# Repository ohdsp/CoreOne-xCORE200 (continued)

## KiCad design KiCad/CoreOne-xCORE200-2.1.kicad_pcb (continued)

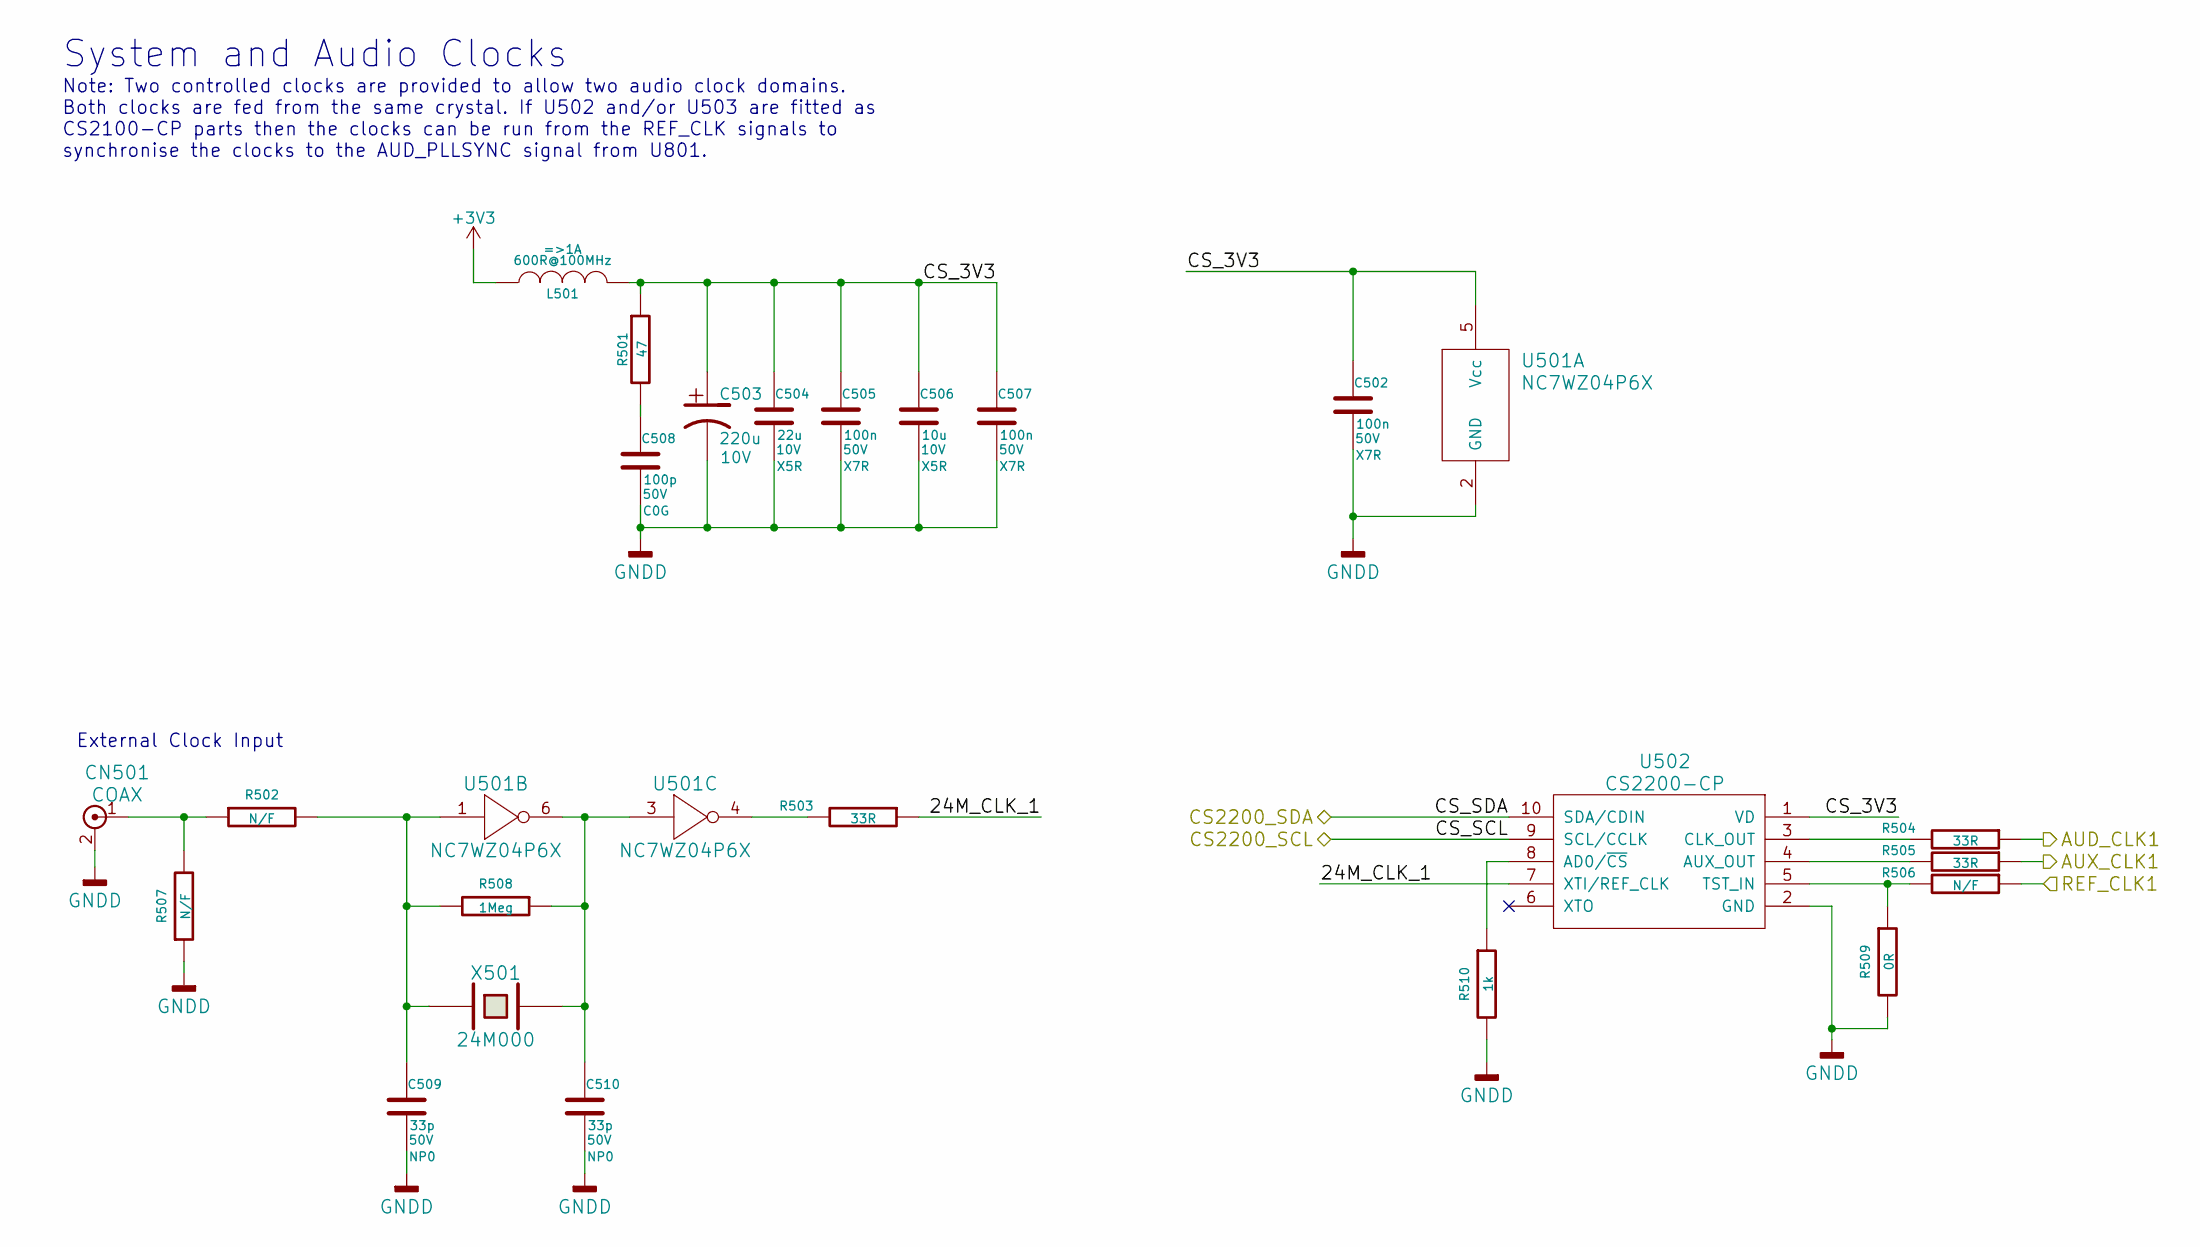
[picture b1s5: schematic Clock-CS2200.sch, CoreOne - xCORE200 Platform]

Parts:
C502, C505, C507: 100n; SMD-0805; Voltage 50V; Tolerance 10%
C503: 220u; CAP-TH-D6.3mmP2.5mm; Voltage 10V
C504: 22u; SMD-0805; Voltage 10V; Tolerance 20%
C506: 10u; SMD-0805; Voltage 10V; Tolerance 20%
C508: 100p; SMD-0805; Voltage 50V; Tolerance 5%
C509, C510: 33p; SMD-0805; Voltage 50V; Tolerance 5%
CN501: COAX; CONN_SIL_2_1MM
L501: 600R@100MHz; SMD-0805
R501: 47; SMD-0805; Tolerance 1%
R502, R506, R507: N/F; SMD-0805; Tolerance 1%
R503, R504, R505: 33R; SMD-0805; Tolerance 1%
R508: 1Meg; SMD-0805; Tolerance 1%
R509: 0R; SMD-0805; Tolerance 1%
R510: 1k; SMD-0805; Tolerance 1%
U501: NC7WZ04P6X; IC-SC70-6
U502: CS2200-CP; IC-MSOP-10
X501: 24M000; XTAL_HC49_TH

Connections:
/AUD_CLK1: R504.1; also elsewhere on the board
/AUD_PLLSYNC: R506.1; also elsewhere on the board
/Clock-CS2200/24M_CLK_1: R503.1, U502.7 (XTI/REF_CLK)
/Clock-CS2200/CS_3V3: C502.1, C503.1, C504.1, C505.1, C506.1, C507.1, L501.2, R501.1, U501.5 (Vcc), U502.1 (VD)
/I2C1_SCL: U502.9 (SCL/CCLK); also elsewhere on the board
/I2C1_SDA: U502.10 (SDA/CDIN); also elsewhere on the board
/SYS_CLK: R505.1; also elsewhere on the board
GNDD: C502.2, C503.2, C504.2, C505.2, C506.2, C507.2, C508.2, C509.2, C510.2, CN501.2, R507.1, R509.2, R510.2, U501.2 (GND), U502.2 (GND); also elsewhere on the board
unnamed: C508.1, R501.2
unnamed: C509.1, R502.2, R508.2, U501.1, X501.1
unnamed: C510.1, R508.1, U501.3, U501.6, X501.2
unnamed: CN501.1, R502.1, R507.2
unnamed: R503.2, U501.4
unnamed: R504.2, U502.3 (CLK_OUT)
unnamed: R505.2, U502.4 (AUX_OUT)
unnamed: R506.2, R509.1, U502.5 (TST_IN)
unnamed: R510.1, U502.8 (AD0/~CS~)

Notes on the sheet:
System and Audio Clocks
External Clock Input
Note: Two controlled clocks are provided to allow two audio clock domains. Both clocks are fed from the same crystal. If U502 and/or U503 are fitted as CS2100-CP parts then the clocks can be run from the REF_CLK signals to synchronise the clocks to the AUD_PLLSYNC signal from U801.

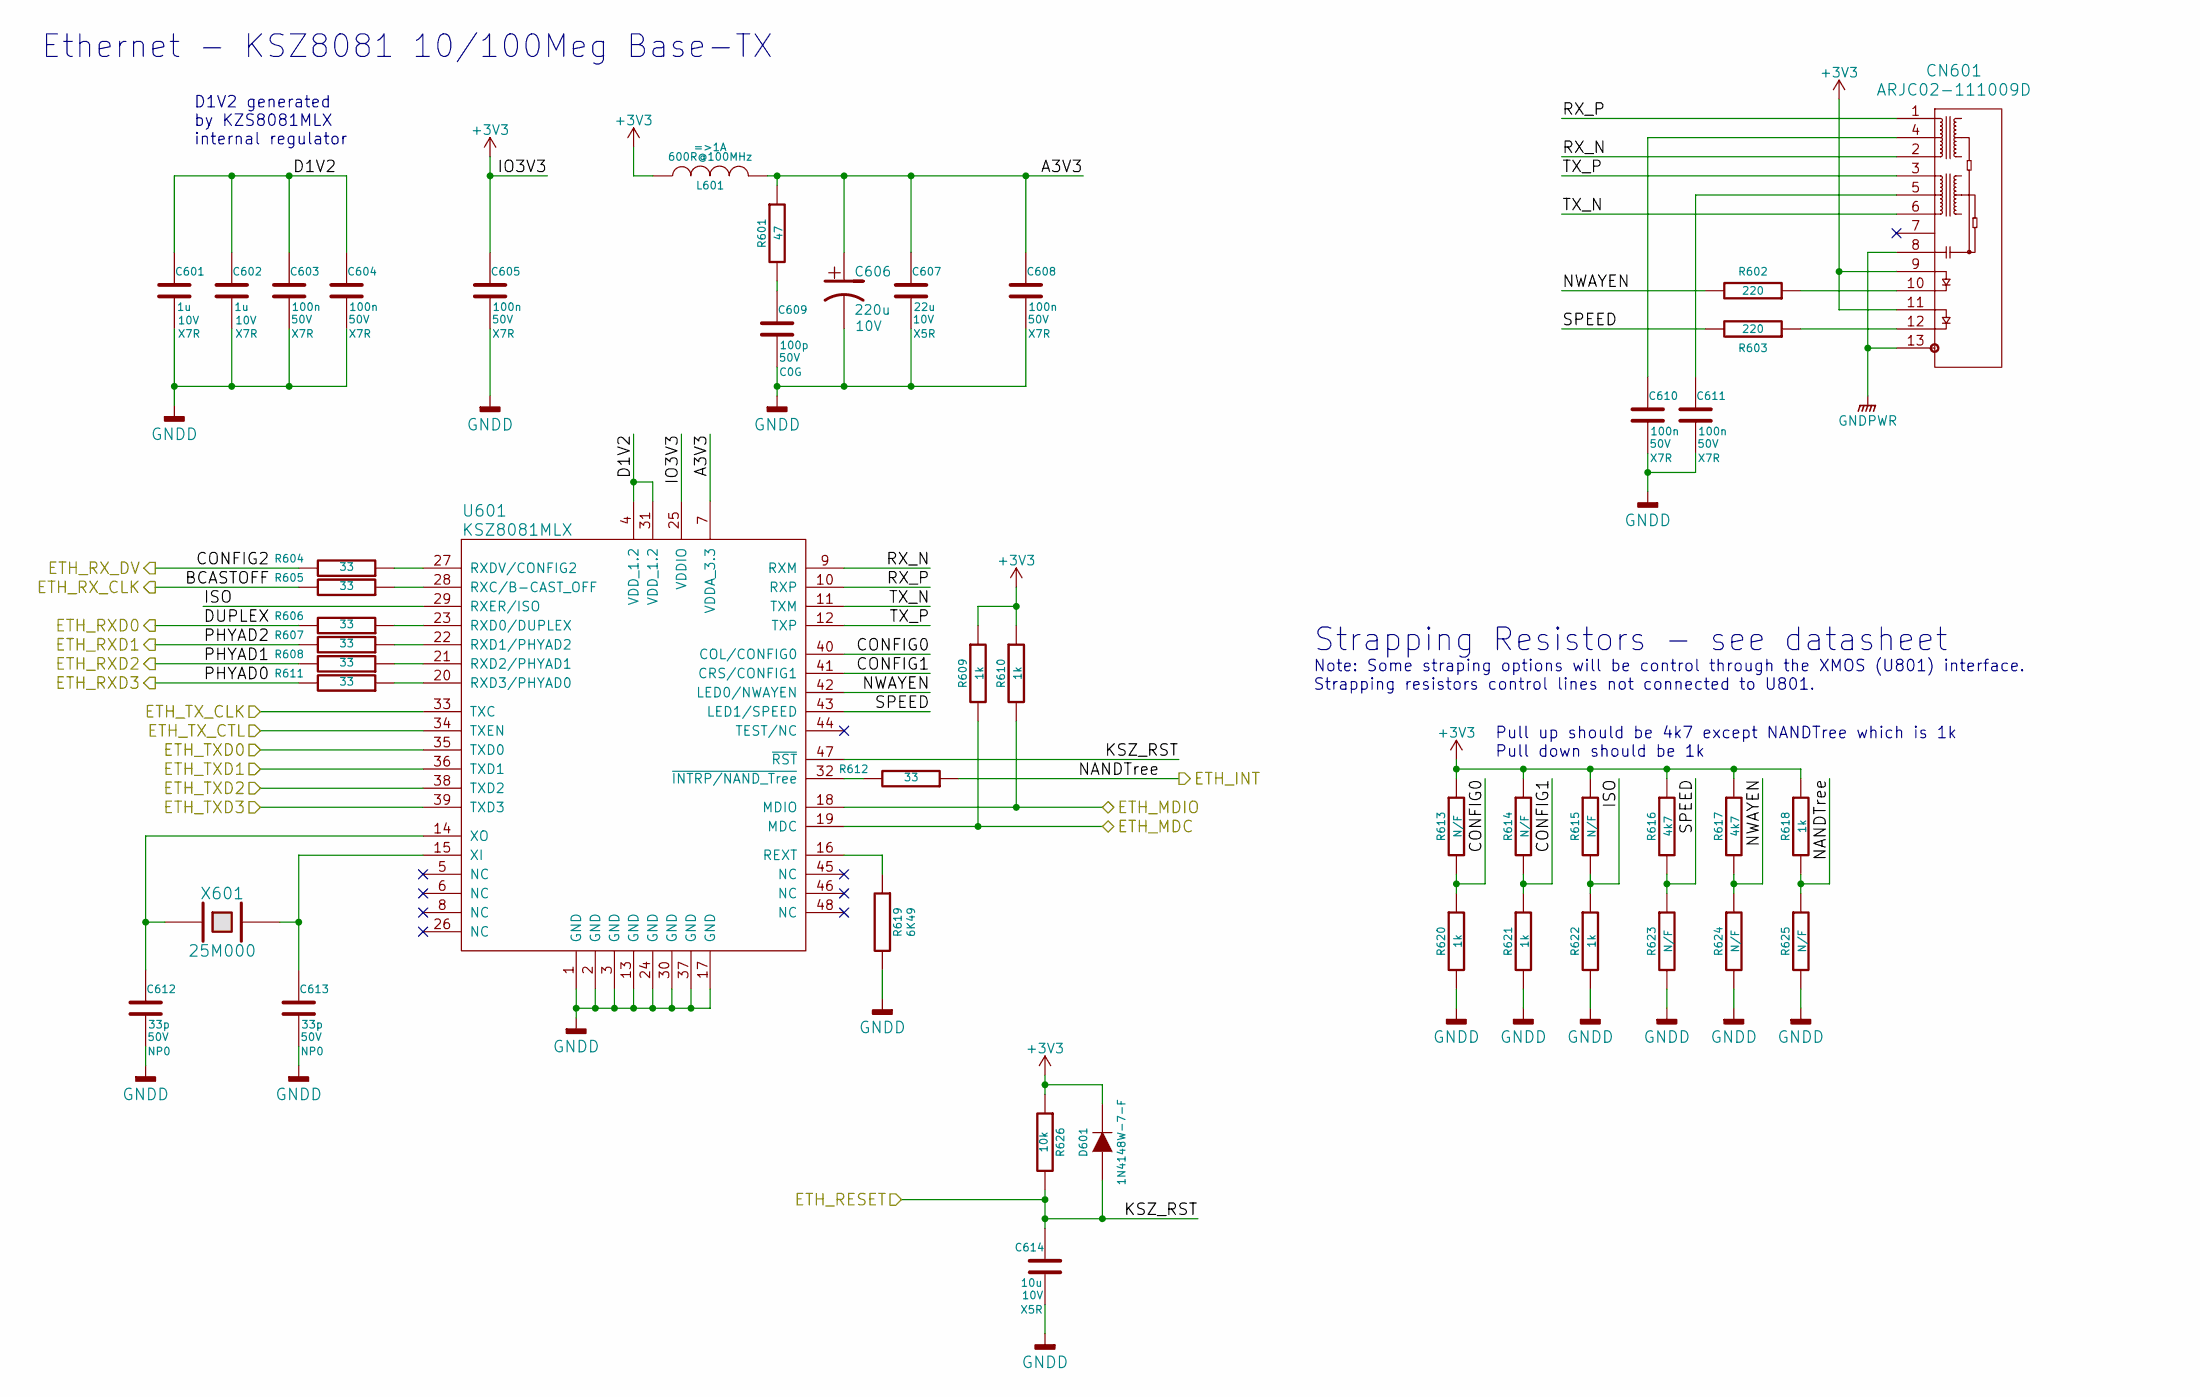
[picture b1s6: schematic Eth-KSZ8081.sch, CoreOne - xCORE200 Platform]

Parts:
C601, C602: 1u; SMD-0805; Voltage 10V; Tolerance 10%
C603, C604, C605, C608, C610, C611: 100n; SMD-0805; Voltage 50V; Tolerance 10%
C606: 220u; CAP-TH-D6.3mmP2.5mm; Voltage 10V
C607: 22u; SMD-0805; Voltage 10V; Tolerance 20%
C609: 100p; SMD-0805; Voltage 50V; Tolerance 5%
C612, C613: 33p; SMD-0805; Voltage 50V; Tolerance 5%
C614: 10u; SMD-0805; Voltage 10V; Tolerance 20%
CN601: ARJC02-111009D; CONN-RJ45-ARJC02-111xxxx
D601: 1N4148W-7-F; DIODE-SOD-123
L601: 600R@100MHz; SMD-0805
R601: 47; SMD-0805; Tolerance 1%
R602, R603: 220; SMD-0805; Tolerance 1%
R604, R605, R606, R607, R608, R611, R612: 33; SMD-0805; Tolerance 1%
R609, R610, R618, R620, R621, R622: 1k; SMD-0805; Tolerance 1%
R613, R614, R615, R623, R624, R625: N/F; SMD-0805; Tolerance 1%
R616, R617: 4k7; SMD-0805; Tolerance 1%
R619: 6K49; SMD-0805; Tolerance 1%
R626: 10k; SMD-0805; Tolerance 1%
U601: KSZ8081MLX; IC-LQFP48_7x7
X601: 25M000; XTAL_HC49_TH

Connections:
/ETH_INT: R612.1, R618.2, R625.1; also elsewhere on the board
/ETH_MDC: R609.2, U601.19 (MDC); also elsewhere on the board
/ETH_MDIO: R610.2, U601.18 (MDIO); also elsewhere on the board
/ETH_RST: C614.1, D601.1 (A), R626.2, U601.47 (~RST~); also elsewhere on the board
/ETH_RX0: R606.2; also elsewhere on the board
/ETH_RX1: R607.2; also elsewhere on the board
/ETH_RX2: R608.2; also elsewhere on the board
/ETH_RX3: R611.2; also elsewhere on the board
/ETH_RX_CLK: R605.2; also elsewhere on the board
/ETH_RX_CTL: R604.2; also elsewhere on the board
/ETH_TX0: U601.35 (TXD0); also elsewhere on the board
/ETH_TX1: U601.36 (TXD1); also elsewhere on the board
/ETH_TX2: U601.38 (TXD2); also elsewhere on the board
/ETH_TX3: U601.39 (TXD3); also elsewhere on the board
/ETH_TX_CLK: U601.33 (TXC); also elsewhere on the board
/ETH_TX_CTL: U601.34 (TXEN); also elsewhere on the board
/Eth-KSZ8081/A3V3: C606.1, C607.1, C608.1, L601.2, R601.1, U601.7 (VDDA_3.3)
/Eth-KSZ8081/CONFIG0: R613.2, R620.1, U601.40 (COL/CONFIG0)
/Eth-KSZ8081/CONFIG1: R614.2, R621.1, U601.41 (CRS/CONFIG1)
/Eth-KSZ8081/D1V2: C601.1, C602.1, C603.1, C604.1, U601.4 (VDD_1.2), U601.31 (VDD_1.2)
/Eth-KSZ8081/ISO: R615.2, R622.1, U601.29 (RXER/ISO)
/Eth-KSZ8081/NWAYEN: R602.2, R617.2, R624.1, U601.42 (LED0/NWAYEN)
/Eth-KSZ8081/RX_N: CN601.2, U601.9 (RXM)
/Eth-KSZ8081/RX_P: CN601.1, U601.10 (RXP)
/Eth-KSZ8081/SPEED: R603.2, R616.2, R623.1, U601.43 (LED1/SPEED)
/Eth-KSZ8081/TX_N: CN601.6, U601.11 (TXM)
/Eth-KSZ8081/TX_P: CN601.3, U601.12 (TXP)
GNDD: C601.2, C602.2, C603.2, C604.2, C605.2, C606.2, C607.2, C608.2, C609.2, C610.2, C611.2, C612.2, C613.2, C614.2, R619.2, R620.2, R621.2, R622.2, R623.2, R624.2, R625.2, U601.1 (GND), U601.2 (GND), U601.3 (GND), U601.13 (GND), U601.17 (GND), U601.24 (GND), U601.30 (GND), U601.37 (GND); also elsewhere on the board
GNDPWR: CN601.8, CN601.13; also elsewhere on the board
unnamed: C609.1, R601.2
unnamed: C610.1, CN601.4
unnamed: C611.1, CN601.5
unnamed: C612.1, U601.14 (XO), X601.1
unnamed: C613.1, U601.15 (XI), X601.2
unnamed: CN601.10, R602.1
unnamed: CN601.12, R603.1
unnamed: R604.1, U601.27 (RXDV/CONFIG2)
unnamed: R605.1, U601.28 (RXC/B-CAST_OFF)
unnamed: R606.1, U601.23 (RXD0/DUPLEX)
unnamed: R607.1, U601.22 (RXD1/PHYAD2)
unnamed: R608.1, U601.21 (RXD2/PHYAD1)
unnamed: R611.1, U601.20 (RXD3/PHYAD0)
unnamed: R612.2, U601.32 (~INTRP/NAND_Tree~)
unnamed: R619.1, U601.16 (REXT)

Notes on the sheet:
Strapping Resistors - see datasheet
Pull up should be 4k7 except NANDTree which is 1k Pull down should be 1k
Ethernet - KSZ8081 10/100Meg Base-TX
Note: Some straping options will be control through the XMOS (U801) interface. Strapping resistors control lines not connected to U801.
D1V2 generated by KZS8081MLX internal regulator

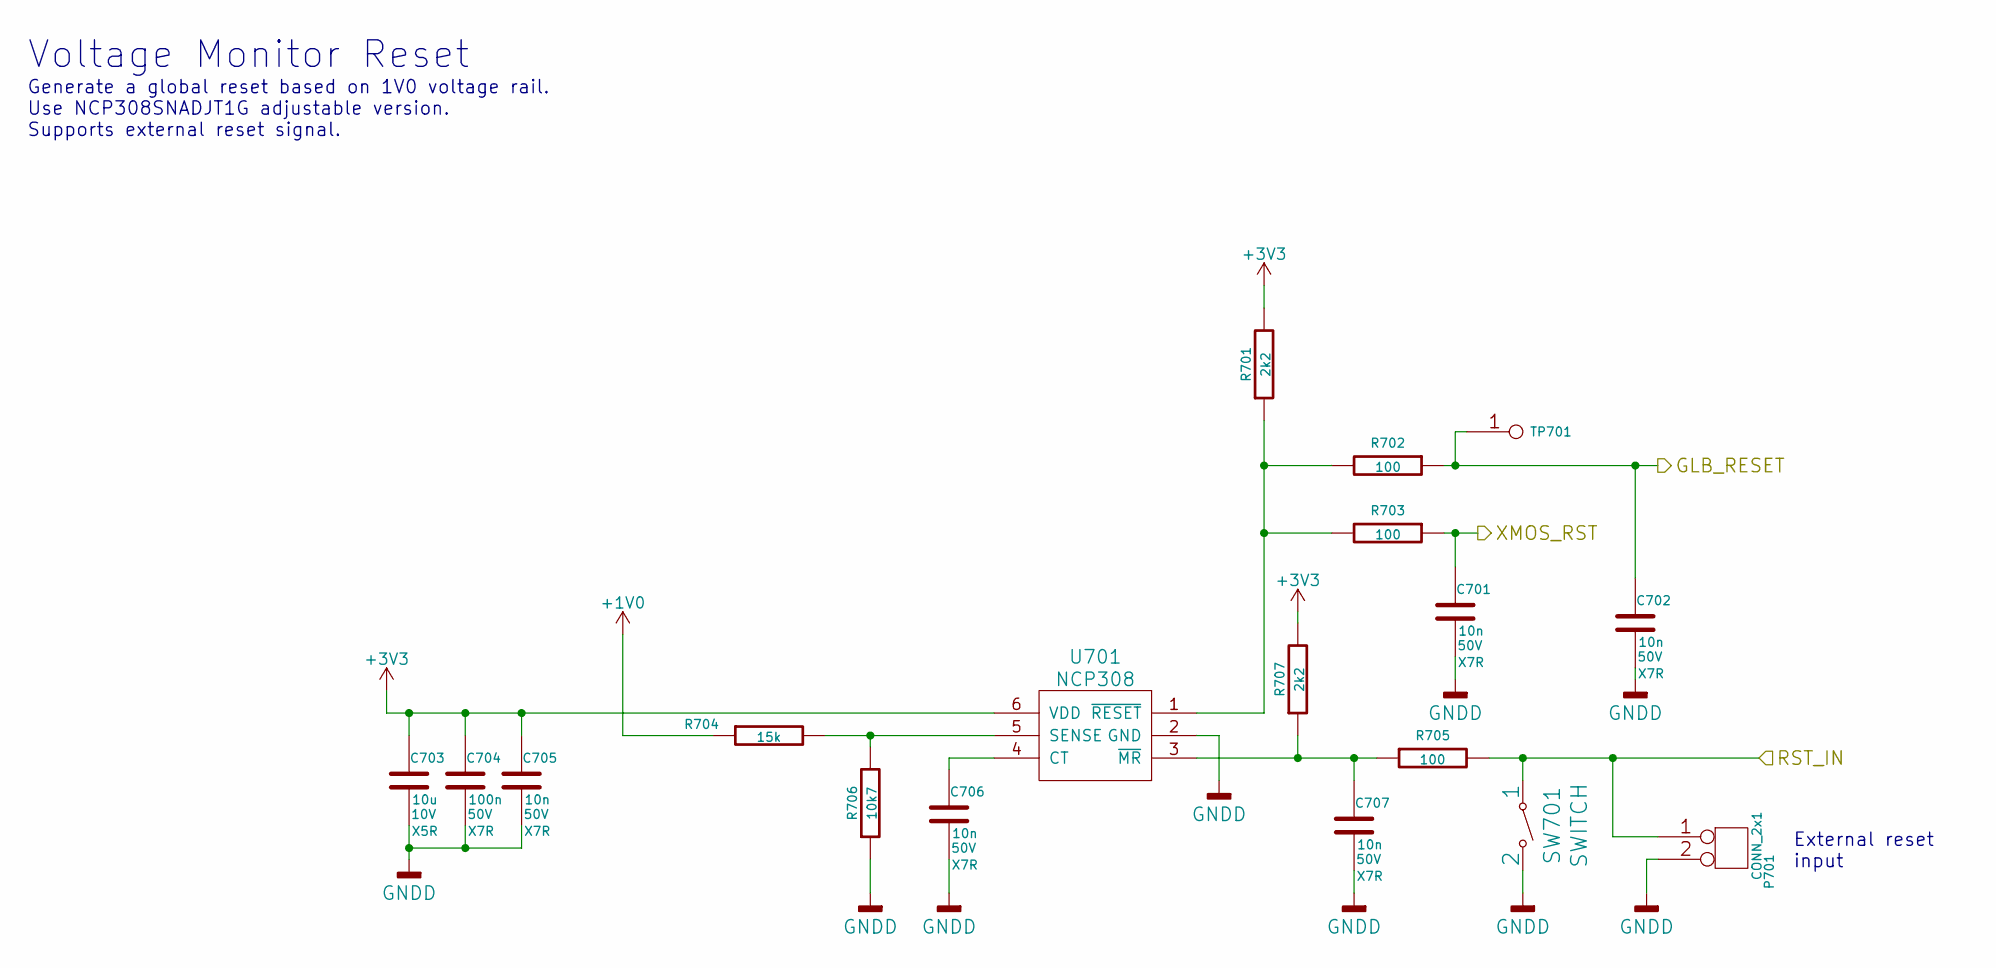
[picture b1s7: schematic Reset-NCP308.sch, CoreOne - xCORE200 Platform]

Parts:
C701, C702, C705, C706, C707: 10n; SMD-0805; Voltage 50V; Tolerance 10%
C703: 10u; SMD-0805; Voltage 10V; Tolerance 20%
C704: 100n; SMD-0805; Voltage 50V; Tolerance 10%
P701: CONN_2x1; CONN_SIL_2_1MM
R701, R707: 2k2; SMD-0805; Tolerance 1%
R702, R703, R705: 100; SMD-0805; Tolerance 1%
R704: 15k; SMD-0805; Tolerance 1%
R706: 10k7; SMD-0805; Tolerance 1%
SW701: SWITCH; SW_TACT_SMD
TP701: PIN; TP-2mm
U701: NCP308; IC-SOT23-6

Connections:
+1V0: R704.1; also elsewhere on the board
/GLB_RST: C702.1, R702.1, TP701.1; also elsewhere on the board
/XMOS_RST: C701.1, R703.1; also elsewhere on the board
/XSYS_RST: P701.1, R705.2, SW701.1; also elsewhere on the board
GNDD: C701.2, C702.2, C703.2, C704.2, C705.2, C706.2, C707.2, P701.2, R706.1, SW701.2, U701.2 (GND); also elsewhere on the board
unnamed: C706.1, U701.4 (CT)
unnamed: C707.1, R705.1, R707.1, U701.3 (~MR)
unnamed: R701.1, R702.2, R703.2, U701.1 (~RESET)
unnamed: R704.2, R706.2, U701.5 (SENSE)

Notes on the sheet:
Generate a global reset based on 1V0 voltage rail. Use NCP308SNADJT1G adjustable version. Supports external reset signal.
Voltage Monitor Reset
External reset input

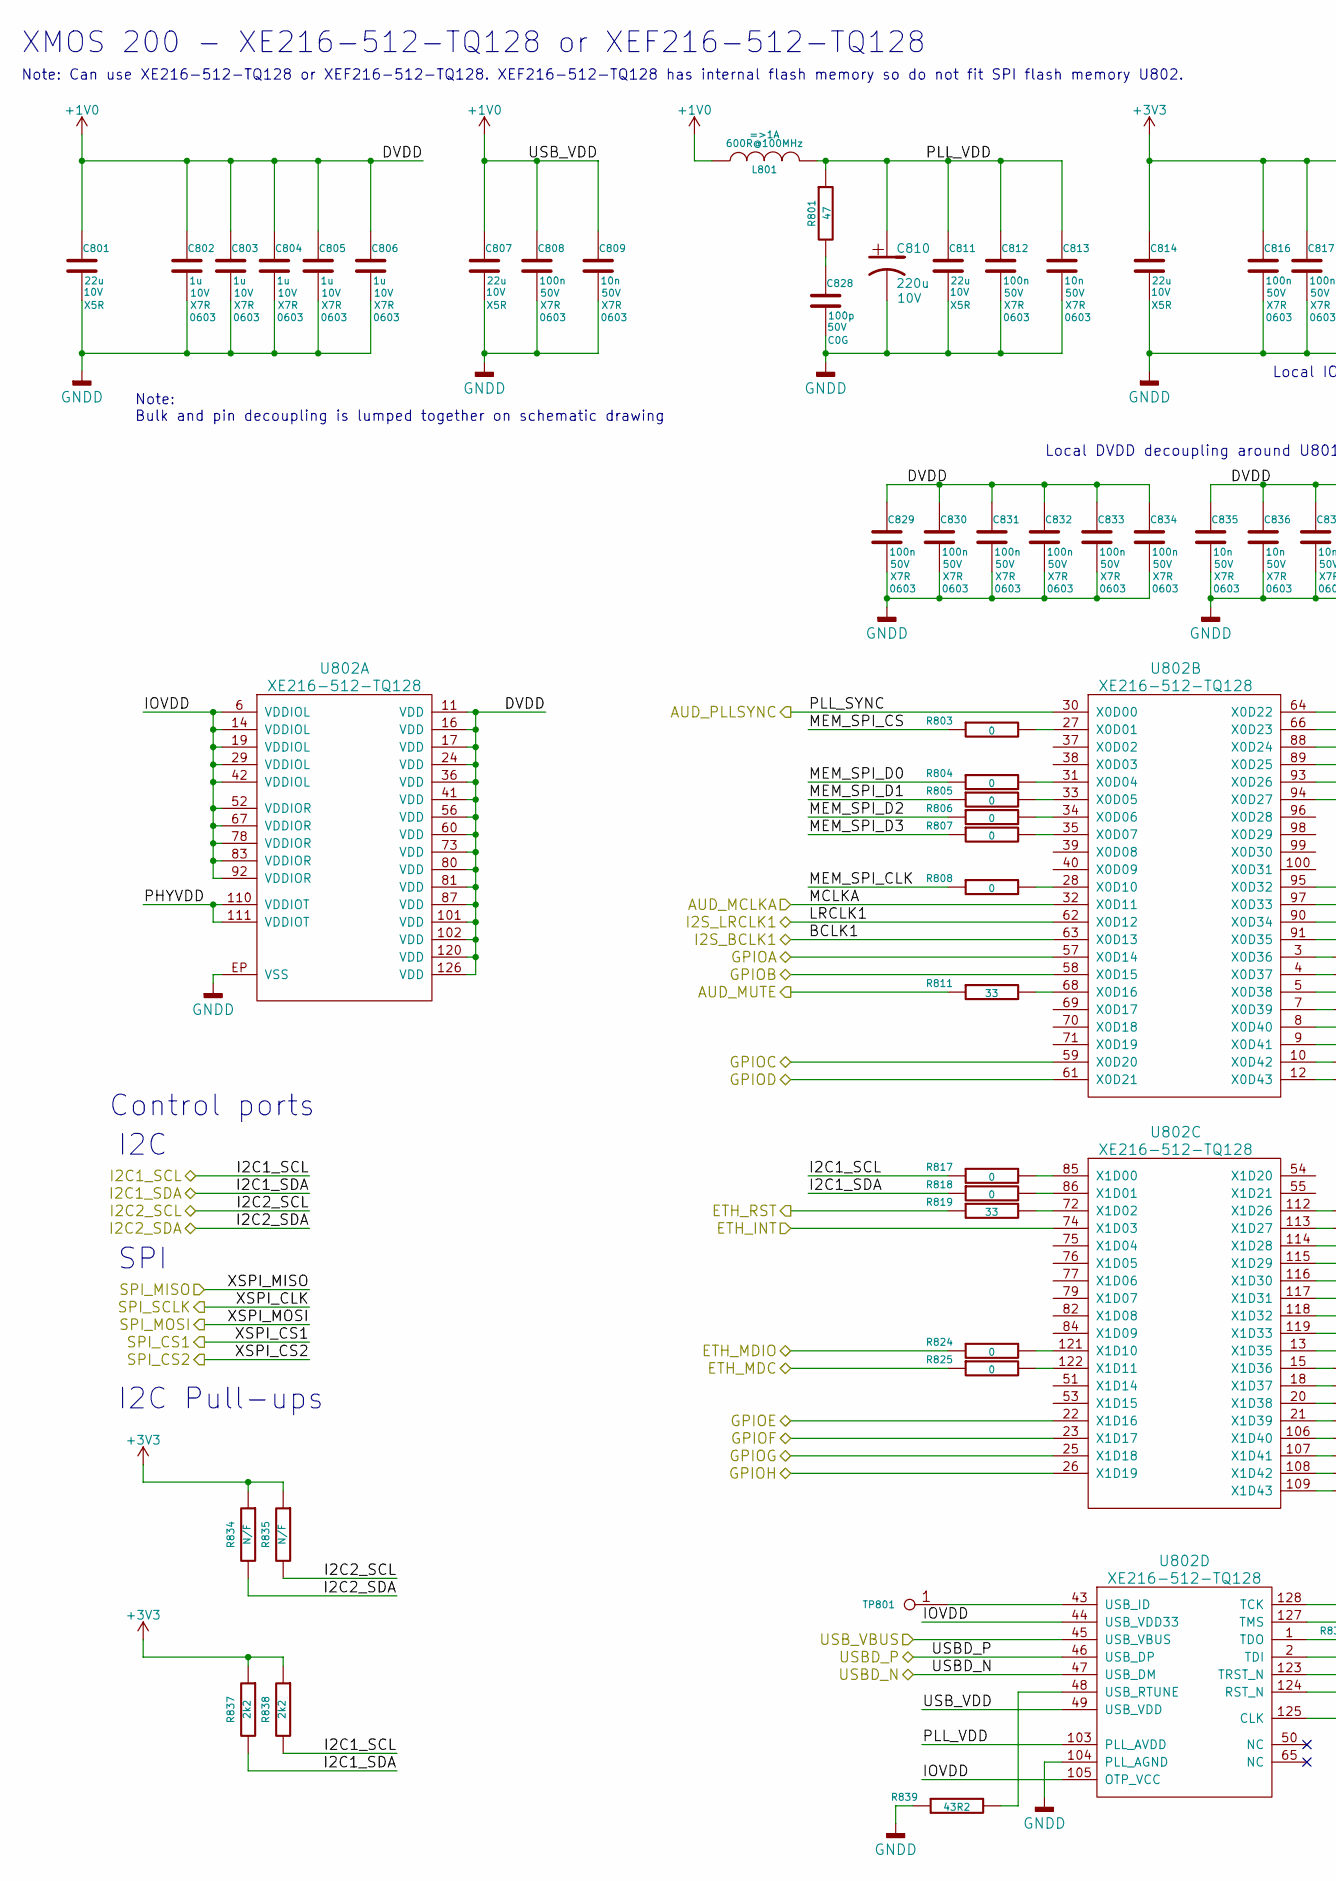
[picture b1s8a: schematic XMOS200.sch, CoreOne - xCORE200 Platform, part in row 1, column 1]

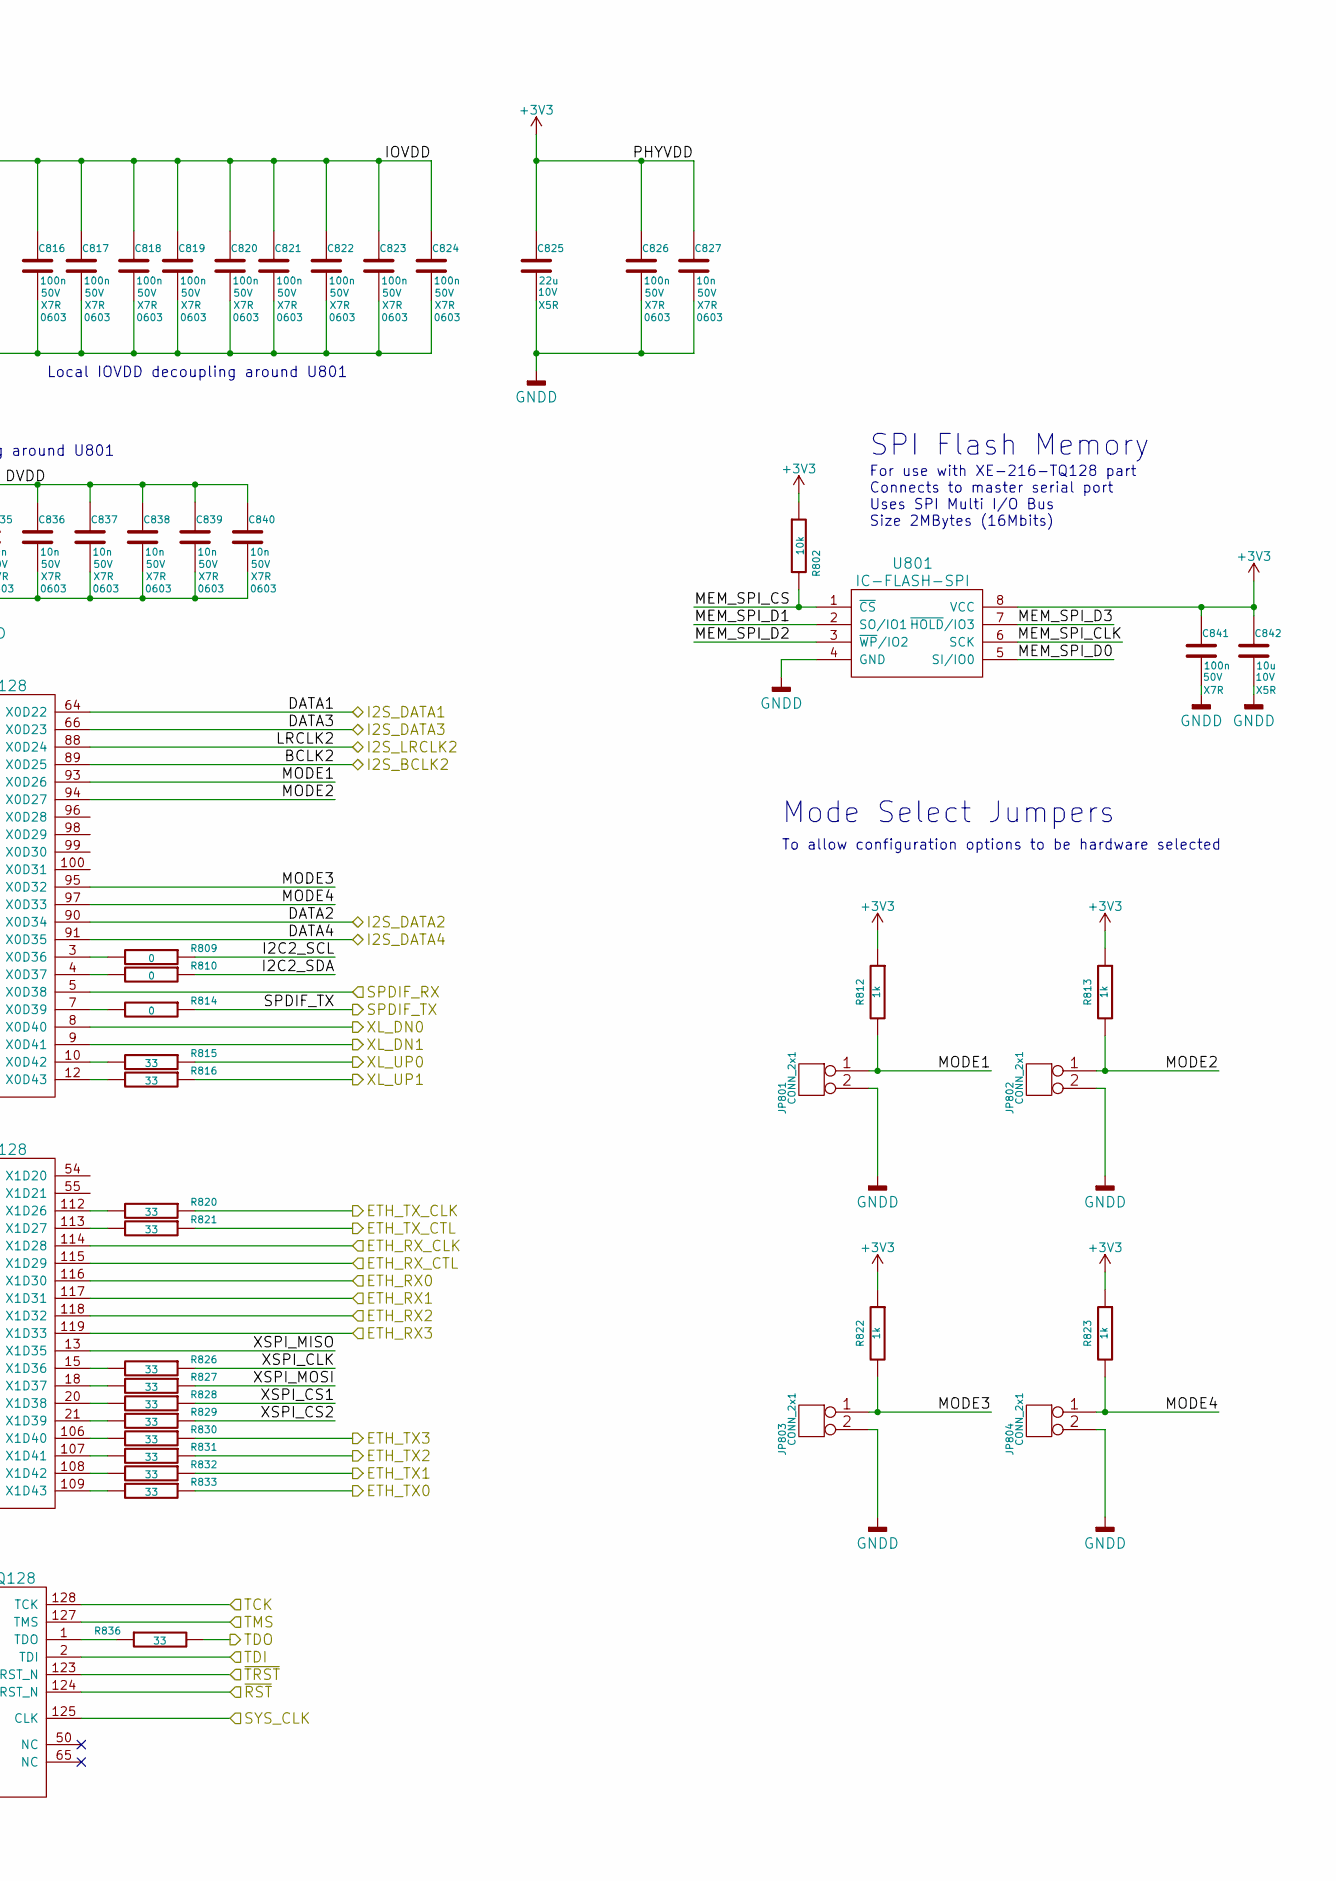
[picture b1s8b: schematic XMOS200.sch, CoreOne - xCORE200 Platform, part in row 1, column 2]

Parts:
C801, C807, C811, C814, C825: 22u; SMD-0805; Voltage 10V; Tolerance 20%
C802, C803, C804, C805, C806: 1u; SMD-0603; Voltage 10V; Tolerance 10%
C808, C812, C816, C817, C818, C819, C820, C821, C822, C823, C824, C826, C829, C830, C831, C832, C833, C834: 100n; SMD-0603; Voltage 50V; Tolerance 10%
C809, C813, C827, C835, C836, C837, C838, C839, C840: 10n; SMD-0603; Voltage 50V; Tolerance 10%
C810: 220u; CAP-TH-D6.3mmP2.5mm; Voltage 10V
C828: 100p; SMD-0805; Voltage 50V; Tolerance 5%
C841: 100n; SMD-0805; Voltage 50V; Tolerance 10%
C842: 10u; SMD-0805; Voltage 10V; Tolerance 20%
JP801, JP802, JP803, JP804: CONN_2x1; CONN_SIL_2_1MM
L801: 600R@100MHz; SMD-0805
R801: 47; SMD-0805; Tolerance 1%
R802: 10k; SMD-0805; Tolerance 1%
R803, R804, R805, R806, R807, R808, R809, R810, R814, R817, R818, R824, R825: 0; SMD-0805; Tolerance 1%
R811, R815, R816, R819, R820, R821, R826, R827, R828, R829, R830, R831, R832, R833, R836: 33; SMD-0805; Tolerance 1%
R812, R813, R822, R823: 1k; SMD-0805; Tolerance 1%
R834, R835: N/F; SMD-0805; Tolerance 1%
R837, R838: 2k2; SMD-0805; Tolerance 1%
R839: 43R2; SMD-0805; Tolerance 1%
TP801: PIN; TP-1mm
U801: IC-FLASH-SPI; IC_SOIC_8
U802: XE216-512-TQ128; IC-TQ128-XMOS-HF

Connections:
+1V0: C801.1, C802.1, C803.1, C804.1, C805.1, C806.1, C807.1, C808.1, C809.1, C829.1, C830.1, C831.1, C832.1, C833.1, C834.1, C835.1, C836.1, C837.1, C838.1, C839.1, C840.1, L801.1, U802.11 (VDD), U802.16 (VDD), U802.17 (VDD), U802.24 (VDD), U802.36 (VDD), U802.41 (VDD), U802.49 (USB_VDD), U802.56 (VDD), U802.60 (VDD), U802.73 (VDD), U802.80 (VDD), U802.81 (VDD), U802.87 (VDD), U802.101 (VDD), U802.102 (VDD), U802.120 (VDD), U802.126 (VDD); also elsewhere on the board
/AUD_CLK1: U802.32 (X0D11); also elsewhere on the board
/AUD_MUTE: R811.1; also elsewhere on the board
/AUD_PLLSYNC: U802.30 (X0D00); also elsewhere on the board
/AUX_DIGI0: U802.57 (X0D14); also elsewhere on the board
/AUX_DIGI1: U802.58 (X0D15); also elsewhere on the board
/AUX_DIGI2: U802.59 (X0D20); also elsewhere on the board
/AUX_DIGI3: U802.61 (X0D21); also elsewhere on the board
/AUX_DIGI4: U802.22 (X1D16); also elsewhere on the board
/AUX_DIGI5: U802.23 (X1D17); also elsewhere on the board
/AUX_DIGI6: U802.25 (X1D18); also elsewhere on the board
/AUX_DIGI7: U802.26 (X1D19); also elsewhere on the board
/ETH_INT: U802.74 (X1D03); also elsewhere on the board
/ETH_MDC: R825.1; also elsewhere on the board
/ETH_MDIO: R824.1; also elsewhere on the board
/ETH_RST: R819.1; also elsewhere on the board
/ETH_RX0: U802.116 (X1D30); also elsewhere on the board
/ETH_RX1: U802.117 (X1D31); also elsewhere on the board
/ETH_RX2: U802.118 (X1D32); also elsewhere on the board
/ETH_RX3: U802.119 (X1D33); also elsewhere on the board
/ETH_RX_CLK: U802.114 (X1D28); also elsewhere on the board
/ETH_RX_CTL: U802.115 (X1D29); also elsewhere on the board
/ETH_TX0: R833.1; also elsewhere on the board
/ETH_TX1: R832.1; also elsewhere on the board
/ETH_TX2: R831.1; also elsewhere on the board
/ETH_TX3: R830.1; also elsewhere on the board
/ETH_TX_CLK: R820.1; also elsewhere on the board
/ETH_TX_CTL: R821.1; also elsewhere on the board
/I2C1_SCL: R817.1, R838.2; also elsewhere on the board
/I2C1_SDA: R818.1, R837.2; also elsewhere on the board
/I2C2_SCL: R810.1, R834.2; also elsewhere on the board
/I2C2_SDA: R809.1, R835.2; also elsewhere on the board
/I2S_BCLK1: U802.63 (X0D13); also elsewhere on the board
/I2S_BCLK2: U802.89 (X0D25); also elsewhere on the board
/I2S_D3: U802.66 (X0D23); also elsewhere on the board
/I2S_D4: U802.91 (X0D35); also elsewhere on the board
/I2S_LRCLK1: U802.62 (X0D12); also elsewhere on the board
/I2S_LRCLK2: U802.88 (X0D24); also elsewhere on the board
/I2S_SDATA1: U802.64 (X0D22); also elsewhere on the board
/I2S_SDATA2: U802.90 (X0D34); also elsewhere on the board
/SPDIF_RX: U802.5 (X0D38); also elsewhere on the board
/SPDIF_TX: R814.1; also elsewhere on the board
/SPI_CS1: R828.1; also elsewhere on the board
/SPI_CS2: R829.1; also elsewhere on the board
/SPI_MISO: U802.13 (X1D35); also elsewhere on the board
/SPI_MOSI: R827.1; also elsewhere on the board
/SPI_SCLK: R826.1; also elsewhere on the board
/SYS_CLK: U802.125 (CLK); also elsewhere on the board
/TCK: U802.128 (TCK); also elsewhere on the board
/TDI: U802.2 (TDI); also elsewhere on the board
/TDO: R836.2; also elsewhere on the board
/TMS: U802.127 (TMS); also elsewhere on the board
/USBD_N: U802.47 (USB_DM); also elsewhere on the board
/USBD_P: U802.46 (USB_DP); also elsewhere on the board
/USB_VBUS: U802.45 (USB_VBUS); also elsewhere on the board
/XL_DN0: U802.8 (X0D40); also elsewhere on the board
/XL_DN1: U802.9 (X0D41); also elsewhere on the board
/XL_UP0: R815.1; also elsewhere on the board
/XL_UP1: R816.1; also elsewhere on the board
/XMOS200/MEM_SPI_CLK: R808.1, U801.6 (SCK)
/XMOS200/MEM_SPI_CS: R802.2, R803.1, U801.1 (~CS)
/XMOS200/MEM_SPI_D0: R804.1, U801.5 (SI/IO0)
/XMOS200/MEM_SPI_D1: R805.1, U801.2 (SO/IO1)
/XMOS200/MEM_SPI_D2: R806.1, U801.3 (~WP~/IO2)
/XMOS200/MEM_SPI_D3: R807.1, U801.7 (~HOLD~/IO3)
/XMOS200/MODE1: JP801.1, R812.2, U802.93 (X0D26)
/XMOS200/MODE2: JP802.1, R813.2, U802.94 (X0D27)
/XMOS200/MODE3: JP803.1, R822.2, U802.95 (X0D32)
/XMOS200/MODE4: JP804.1, R823.2, U802.97 (X0D33)
/XMOS200/PLL_VDD: C810.1, C811.1, C812.1, C813.1, L801.2, R801.1, U802.103 (PLL_AVDD)
/XMOS200/~TRST~: U802.123 (TRST_N); also elsewhere on the board
/XMOS_RST: U802.124 (RST_N); also elsewhere on the board
GNDD: C801.2, C802.2, C803.2, C804.2, C805.2, C806.2, C807.2, C808.2, C809.2, C810.2, C811.2, C812.2, C813.2, C814.2, C816.2, C817.2, C818.2, C819.2, C820.2, C821.2, C822.2, C823.2, C824.2, C825.2, C826.2, C827.2, C828.2, C829.2, C830.2, C831.2, C832.2, C833.2, C834.2, C835.2, C836.2, C837.2, C838.2, C839.2, C840.2, C841.2, C842.2, JP801.2, JP802.2, JP803.2, JP804.2, R839.1, U801.4 (GND), U802.104 (PLL_AGND), U802.EP (VSS); also elsewhere on the board
unnamed: C828.1, R801.2
unnamed: R803.2, U802.27 (X0D01)
unnamed: R804.2, U802.31 (X0D04)
unnamed: R805.2, U802.33 (X0D05)
unnamed: R806.2, U802.34 (X0D06)
unnamed: R807.2, U802.35 (X0D07)
unnamed: R808.2, U802.28 (X0D10)
unnamed: R809.2, U802.3 (X0D36)
unnamed: R810.2, U802.4 (X0D37)
unnamed: R811.2, U802.68 (X0D16)
unnamed: R814.2, U802.7 (X0D39)
unnamed: R815.2, U802.10 (X0D42)
unnamed: R816.2, U802.12 (X0D43)
unnamed: R817.2, U802.85 (X1D00)
unnamed: R818.2, U802.86 (X1D01)
unnamed: R819.2, U802.72 (X1D02)
unnamed: R820.2, U802.112 (X1D26)
unnamed: R821.2, U802.113 (X1D27)
unnamed: R824.2, U802.121 (X1D10)
unnamed: R825.2, U802.122 (X1D11)
unnamed: R826.2, U802.15 (X1D36)
unnamed: R827.2, U802.18 (X1D37)
unnamed: R828.2, U802.20 (X1D38)
unnamed: R829.2, U802.21 (X1D39)
unnamed: R830.2, U802.106 (X1D40)
unnamed: R831.2, U802.107 (X1D41)
unnamed: R832.2, U802.108 (X1D42)
unnamed: R833.2, U802.109 (X1D43)
unnamed: R836.1, U802.1 (TDO)
unnamed: R839.2, U802.48 (USB_RTUNE)
unnamed: TP801.1, U802.43 (USB_ID)

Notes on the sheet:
Mode Select Jumpers
To allow configuration options to be hardware selected
I2C Pull-ups
I2C
Control ports
SPI
XMOS 200 - XE216-512-TQ128 or XEF216-512-TQ128
For use with XE-216-TQ128 part Connects to master serial port Uses SPI Multi I/O Bus Size 2MBytes (16Mbits)
SPI Flash Memory
Local DVDD decoupling around U801
Local IOVDD decoupling around U801
Note: Bulk and pin decoupling is lumped together on schematic drawing
Note: Can use XE216-512-TQ128 or XEF216-512-TQ128. XEF216-512-TQ128 has internal flash memory so do not fit SPI flash memory U802.

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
